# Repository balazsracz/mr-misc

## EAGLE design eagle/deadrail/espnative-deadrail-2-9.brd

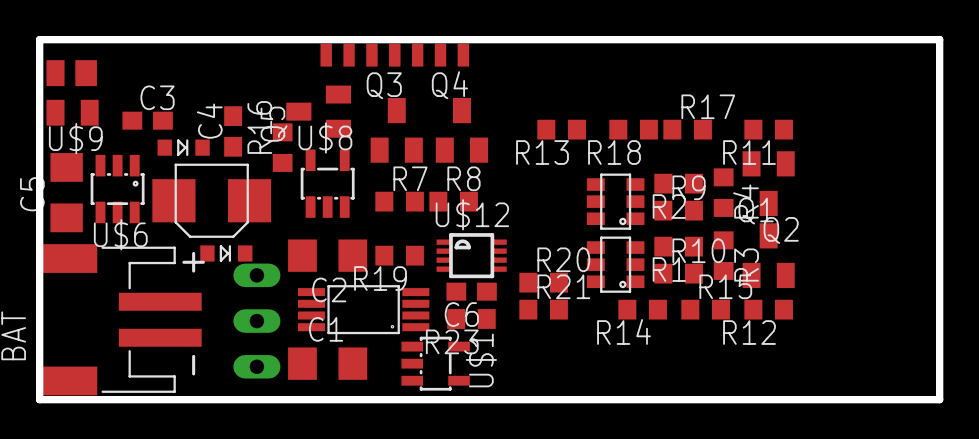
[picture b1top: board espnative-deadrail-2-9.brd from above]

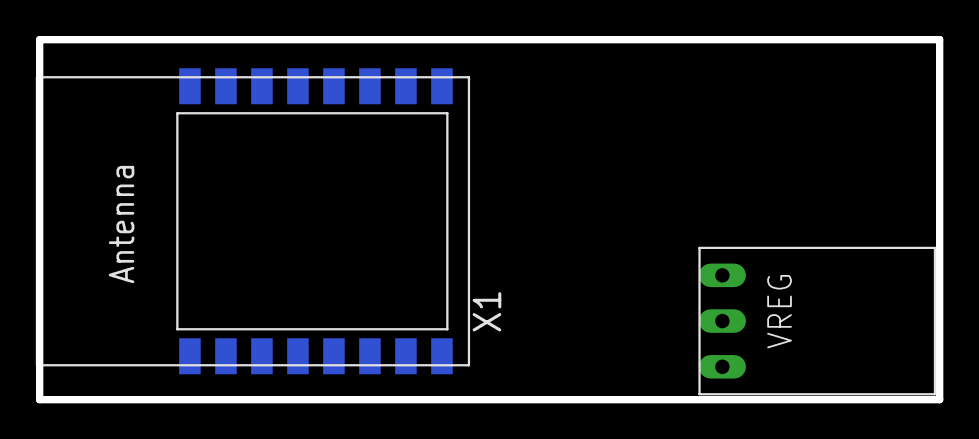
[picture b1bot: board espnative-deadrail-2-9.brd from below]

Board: 2 copper layers, 50.0 x 20.0 mm, 46 parts (2 on the bottom side), 36 nets, no tracks yet.

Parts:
BAT: JST-PH-2-SMT-RA
C1, C2: C1206
C3: 1 uF; C0603
C4: 22uF; C0603
C5: 22uF; C1206
C6: 10n; C0603
L1: 10uH; FDSD0420
Q1, Q2, Q3, Q4, Q5: BSS123; SOT23
R1, R2: 5k; R0603
R3, R4, R13, R15, R17, R18: 10k; R0603
R7, R9, R10, R11, R12, R14: 47k; R0603
R8: 270k; R0603
R16: 2k2; R0603
R19: 500; R0603
R20, R21: 15k; R0603
R23: 1k..5k; R0603
U$1: AP2112K-3V3; SOT23-5L
U$2, U$3: DMG6601-LVT; TSOT-26
U$4: TPS2115A; TSSOP-8
U$5: POLOLU-VREG12; POLOLU-REGULATOR
U$6: LMR16006Y; SOT23-6
U$7, U$11: DIODE; DIODE-1206
U$8: STC4054; SOT23-5L
U$9: BAS3007A; SOT143B
U$10: DECODER-WIRE-PADS7; DECODER-WIRE-PADS
U$12: TS5A3359; US8
X1: ESP-12

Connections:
+3V3: R15.1, R17.1, R18.1, U$1.5, U$12.8, X1.8
+4.1V: U$1.1, U$1.3, U$4.7
+5V: C4.1, L1.P$1, U$4.6, U$6.3, U$8.4
+12V: C2.2, R1.2, R2.2, U$2.2, U$3.2, U$5.VOUT, U$10.4, U$11.C
BAT_EN: R14.1, U$4.2, X1.4
CHRG_EN: Q5.1, R13.1, X1.10
CHRG_FB: R16.1, U$8.5, U$12.2
DCC_VPLUS: C5.2, U$6.5, U$9.4, U$11.A
F0_FRONT: Q3.1, X1.13
F0_REAR: Q4.1, X1.15
GND: BAT.2, C1.2, C2.1, C4.2, C5.1, C6.2, Q1.2, Q2.2, Q3.2, Q4.2, Q5.2, R8.2, R9.2, R10.2, R11.2, R12.1, R13.2, R14.2, R19.2, R23.2, U$1.2, U$2.5, U$3.5, U$4.3, U$4.5, U$5.GND, U$6.2, U$7.C, U$8.2, U$9.1, U$12.4, X1.9
LIGHT_B: Q4.3, U$10.3
LIGHT_F: Q3.3, U$10.5
MOTA_HIGH: Q1.1, R12.2, X1.5
MOTA_LOW: R10.1, U$2.1, X1.6
MOTB_HIGH: Q2.1, R11.1, X1.14
MOTB_LOW: R9.1, U$3.1, X1.7
MOT_A: R21.2, U$2.4, U$2.6, U$10.6
MOT_B: R20.2, U$3.4, U$3.6, U$10.2
MOT_FB: C6.1, R20.1, R21.1, R23.1, U$12.1
unnamed: U$12.7, X1.2
unnamed: R1.1, R3.1, U$2.3
unnamed: Q2.3, R4.2
unnamed: R2.1, R4.1, U$3.3
unnamed: C3.2, L1.P$2, U$6.6, U$7.A
unnamed: Q1.3, R3.2
unnamed: C3.1, U$6.1
unnamed: Q5.3, R16.2
unnamed: R17.2, U$12.6, X1.12
unnamed: R15.2, X1.3
unnamed: R18.2, U$12.5, X1.11
unnamed: R19.1, U$4.4
TRK_L: U$9.2, U$10.7
TRK_R: U$9.3, U$10.1
VBAT: BAT.1, C1.1, R7.1, U$4.8, U$5.VIN, U$8.3
VBAT_FB: R7.2, R8.1, U$12.3
